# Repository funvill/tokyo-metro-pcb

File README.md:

# tokyo-metro-pcb

A printed circuit board that is a map of the Tokyo subway, with one
addressable RGB LED per station: Tokyo Metro's nine lines and Toei's four,
the two extensions under construction, the JR Yamanote loop, the Toden
Arakawa tram, the Yurikamome, the Rinkai line and the Shinkansen —
**248 stations, 248 LEDs**, on a 320 × 280 mm board.

The third board in the series, ported from the
[Montréal Métro PCB](https://github.com/funvill/montreal-skytrain-pcb), which
came from the
[Vancouver SkyTrain PCB](https://github.com/funvill/vancouver-skytrain-pcb).

The map is **organic**: every station stands where the city puts it (mean
error 6 m) and the track follows the real rails from OpenStreetMap, bridges
and tunnels included — the Rainbow Bridge with its Shibaura spiral, the
1,236 m Arakawa truss, the Tokyo Port Tunnel. Station names sit in capsules
that knock the route out behind them, so a name may lie across a line and
still read.

**Status: the map is finished, and the KiCad board is built from it —
placement, outline and artwork. Nothing is routed yet.**

*The KiCad board, rendered by `kicad-cli`. Not a preview: this is the
artwork as it would be plotted.*

## Where things are

| Folder | What |
|---|---|
| [`input/tokyo.json`](input/) | **The board.** Stations, lines, label placements, chain, water, wordmark |
| [`input/`](input/) | The builders, the Overpass queries, and the hand-made data |
| [`input/osm/`](input/osm/) | Raw Overpass responses, committed so builds run offline |
| [`fonts/`](fonts/) | Archivo Narrow SemiBold, the label face, SIL OFL |
| [`tools/`](tools/) | The pipeline: layout, labels, chain, checks, previews, fab outputs |
| [`hardware/`](hardware/) | KiCad 10 footprint and symbol libraries; the board is not built yet |
| [`firmware/`](firmware/) | XIAO firmware; the line table is generated from the data |
| [`docs/decisions.md`](docs/decisions.md) | Scope, board, labels, power, controller |
| [`docs/styles.md`](docs/styles.md) | The eight map styles considered, and everything settled since |
| [`runbook-new-city.md`](runbook-new-city.md) | The phase-by-phase process |
| [`lessons-learned.md`](lessons-learned.md) | Part D is this board; Part C is the pre-order checklist |

## Rebuilding the map

```bash
cd input && ./rebuild.sh
```

One command, from the cached Overpass responses to `tokyo.json` and the
previews. Every intermediate is disposable and none is kept.

Hand work is **not** regenerated: `label_overrides.json` (248 label
placements) and `chain.json` (the LED order) are re-applied on every build,
and the only way to change them is `import_labels.py` or `build_chain.py`,
deliberately (lesson B5).

| Step | Tool |
|---|---|
| Station list from OSM, cross-checked against the official station codes | `input/build_station_latlon.py` |
| Octolinear layout, land fitted rigidly, water, wordmark | `input/build_tokyo.py` |
| Move the board edge in without redrawing the map | `tools/crop_board.py` |
| Label placement | `tools/auto_label.py`, `tools/check_fit.py` |
| LED chain order | `tools/build_chain.py` |
| What the board will etch | `tools/preview_map.py` |
| Firmware line table | `tools/make_firmware_lines.py` |

## The board

| | |
|---|---|
| Size | 320 × 280 mm, 2 layers, ENIG |
| LEDs | 248 XL-1615 WS2812B, one per station |
| Lines | 18, drawn in 0.75 mm white silkscreen on their real alignment; the Shinkansen at 2.2× |
| Water | Bare ENIG copper, land placed rigidly at 14.4 mm/km, north up; no station's clearance disc notches it |
| Labels | English names, 1.1 mm, Archivo Narrow SemiBold **embedded in the board**, each in a knockout capsule; 242 of 248 plain horizontal, none rotated |
| Power | A USB-C input of its own, plus a 2-pin Phoenix Contact terminal block on a cuttable link |
| Controller | Seeed XIAO RP2040, hand-soldered at a board edge |

## Known, going into routing

- **67 LEDs sit in a hole cut out of the water**, so the front ground pour
  will be cut into islands and each of them needs its own via to the back
  plane. Script the island count; do not eyeball it (lesson A5, Part C.5).
- **38 chain hops cross bare-copper water**, 174 mm in total. None can run
  on the front.
- **25 label collisions remain** in the core, all but two white-on-white
  text over a route. They are hand work in KiCad, then frozen with
  `import_labels.py`.
- **248 LEDs is about 15 A at full white.** The firmware cap stays at
  900 mA until the supply and the injection points are proven.

## Still to do

1. Route by hand. Before starting: **67 LEDs sit in a hole cut out of the
   bare-copper water**, so the front pour is in islands and each needs its
   own via to the back plane; and **38 chain hops cross water**, which
   cannot be routed on the front.
2. Clear the DRC that is left: 2 shorts where mounting holes fall in the
   bay, 28 isolated copper islands, 16 starved thermals. The 11 "silkscreen
   clipped by board edge" warnings are the line stubs running off the edge
   on purpose, and the fab trims them.
3. The Part C checklist before ordering.

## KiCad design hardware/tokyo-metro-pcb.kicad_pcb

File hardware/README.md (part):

# Hardware (KiCad 10)

`tokyo-metro-pcb` — 320 × 280 mm, 2 layers, 248 WS2812B LEDs (XL-1615), one
per station, generated from [`../input/tokyo.json`](../input/tokyo.json).

Copied from the Montréal board and ported by the scripts in `../tools`.
**The schematic is built and verified, and the board is placed and has its
artwork. Nothing is routed.**

## State

| | |
|---|---|
| Schematic | 248 LEDs in 13 rows of 20, generated by `make_schematic.py`; 0 duplicate uuids; **0 overlapping symbols, labels or visible text** (`check_schematic.py`); regenerating is idempotent (byte-identical on a second run) |
| Chain | `U1 GPIO1 → LED_DATA → R1 → LED_IN → LED1 … LED248 → LED_OUT`, verified by `check_led_chain.py` — which now checks the **driver**, the **rails** and the **capacitors** too, not just the hops. Each of those was added after a bug it would have caught: the generator deleted `LED_DATA`/`LED_IN` off R1 and put nothing back (R1 floating, nothing driving the chain, PASS); a rail checked by *name* would pass with no source on it; and extending from 13 caps to 52 without extending the power rail left 39 of them floating, also PASS |
| Nets | 256 real nets; +5V 265 nodes, GND 272. 11 single-node nets, all deliberate: seven spare XIAO GPIOs, `3V3`, and the redundant pad of each 4-pad tactile switch |
| Controller | U1 (XIAO RP2040), R1 (330 Ω), C1 (100 µF 6.3 V, 1206), SW1–4, four test points, four M3 holes — all inherited from Montréal, wiring intact. U1's **Value says `XIAO-RP2040-DIP` but its footprint is the SMD/castellated land pattern** — a header module will not fit; reconcile before assembly |
| Decoupling | **52 caps, ROW0–ROW51** at `1uF,16V,X5R` in 0402, four per schematic row, each across the rails and spread along the chain by index so they land across the whole map. Was 13 — one per row of 20 LEDs, which is bulk rather than decoupling: the far LED sat nineteen pitches of trace from its cap and the east of the board was 74 mm from the nearest one. The old value, `10uF,10V,X5R` in an 0402, is not a buyable part; 1 µF 16 V in 0402 is |
| Board | 320 × 280 mm, r5 corners; Montréal's tracks and front art stripped; 1,118 art blocks written; schematic parity clean. One GND zone on F.Cu + B.Cu — there were three stacked copies with identical outlines, whose fills split arbitrarily by priority and accounted for all 32 `isolated_copper` reports |
| DRC | 0 shorts, 0 clearance, 0 isolated copper, 0 parity. Left: 16 `starved_thermal` (GND pads on cut-up islands, routing-stage), 11 `silk_edge_clearance` (art bleeding off the edge — intended, the fab clips it), 199 `solder_mask_bridge`. The mask-bridge check was set to `ignore` and is now `warning`: 199 of its 200 hits are pad-to-pad *inside* one LED footprint, whose own inter-pad gap is 0.250 mm, so this is a fab mask-dam question about the footprint, not an artwork bug |
| Placement | 248 LEDs at their stations, **all at one orientation (270°, pin 1 up)**; 52 decoupling capacitors; 4 M3 holes; controller group at (40, 220). They used to be turned individually so DOUT faced the next in the chain, which gave the router shorter hops but put the parts at eight different angles — and pads 1 and 4 share the part's long edge, so a 180° error swaps GND with DI and +5V with DO. One orientation makes the whole board a single thing to check |
| Routing | **nothing routed** — 547 unconnected pads. Note the DRC *report* says 499: its JSON omits 48 real ratsnest edges (the chain hops that cross the bay, and the four BUTTON nets), so **do not use "unconnected: 0" in the report as the routing-complete gate** — read `GetUnconnectedCount` from pcbnew instead |
| Firmware tables | `firmware_tables.h`: NUM_LEDS 248, 36 line/branch index arrays |

## Regenerating the schematic

```
cd ../tools
python -X utf8 make_schematic.py ../hardware/tokyo-metro-pcb.kicad_sch 248
```

`tokyo-metro-pcb.kicad_sch.template` is a **required input**: a pristine copy
of the Montréal sheet, committed alongside the schematic. The generator always
builds from it, never from its own last output - reading its own output moved
the generated power symbols outside the drop region and left 130 duplicate
uuids on the second run.

It rebuilds the whole LED section — symbols, rails, row decoupling caps,
chain wiring and the `CHAIN1`…`CHAIN12` row labels — and leaves the
controller block and the test-point column untouched. It is safe to re-run:
the second run drops what the first generated and produces the same bytes.

Three things it has to get right, each of which it got wrong first:

- **Keep the controller's wiring.** Dropping every wire on the sheet leaves
  U1, R1 and the test points floating, with nothing on `LED_IN` or
  `LED_OUT`. Only wires below `GRID_TOP` *and* right of `GRID_LEFT` belong
  to the grid; the test-point column runs down to y = 83 at x = 24.
- **Do not reuse Montréal's row label names.** Its last output was tied to
  the `LED_OUT` test point with a second label, `ROW8`. With 13 rows that
  collides, shorting LED160 to the chain output. Generated labels are
  `CHAIN*`, and stray `ROW*` labels are dropped.
- **Re-uuid every uuid in a cloned block**, not just the first. A symbol
  carries one per property, so cloning 248 LEDs left four uuids shared
  across all of them.

## Checking the schematic for overlaps

```
python -X utf8 ../tools/check_schematic.py tokyo-metro-pcb.kicad_sch -v
```

A generated sheet can be electrically perfect and unreadable: nothing in the
netlist notices a decoupling capacitor sitting on a global label, and KiCad's
ERC does not check it either. The checker takes each symbol's outline from
its `lib_symbols` definition, rotates and moves it to the instance, and adds
a box for every global label and every *visible* Reference and Value - the
hidden ones are metadata and counting them buries the real collisions in 900
false ones. It reports 710 placed items and 0 overlapping pairs.

Three overlaps it found, all now fixed in the generator:

- the row capacitors sat on their own row's input label (`x_cap = ox - 30.48`
  moves them clear), and then on the mounting-hole column (grid origin moved
  to `95,70`);
- Montréal's `LED_DATA` and `LED_IN` labels sat directly on R1's body,
  because they were placed on its pins with no wire at all - each now gets a
  5.08 mm stub wire;
- C1's Value text is 16 mm wide and the gap between U1 and the +5V symbol is
  14.5 mm, so it is moved to the clear band below the controller.

## Checking

```
"C:/Program Files/KiCad/10.0/bin/kicad-cli.exe" sch export netlist \
    --format kicadsexpr -o ../test-results/netlist.net tokyo-metro-pcb.kicad_sch
python -X utf8 ../tools/check_led_chain.py ../test-results/netlist.net 248
grep -o 'uuid "[^"]*"' tokyo-metro-pcb.kicad_sch | sort | uniq -d | wc -l   # 0
```

A netlist export that prints no warning means the annotation is clean; a
duplicate `#PWR` reference is what "schematic has annotation errors" means,
so the generated power symbols are numbered from `#PWR901` to stay clear of
the controller's own.

## Still to do

1. **The board.** `port_board.py --strip` on a fresh copy, then
   `reposition_board.py --board 320 --height 280`, then `export_art.py` and
   `mask_under_silk.py`.
2. The hand pass over the 25 remaining label collisions, then
   `import_labels.py` to freeze them.
3. **A way to get power in.** There is none: every `+5V` node is an LED, a
   cap, U1's VBUS, or a 3 × 3 mm test pad. The only real inputs are the
   XIAO's USB-C and two SMD test points, and neither passes amps. This is a
   schematic change plus a board re-import — cheap now, painful after
   routing. Decide the LED current first: 248 × 60 mA (the 5050 WS2812B
   figure) is 15 A, but the XL-1615 is a 1.6 × 1.5 mm part and is likely
   well under 20 mA full-white, which would put the board nearer 4–5 A. No
   datasheet is in the repo and the symbol's Datasheet field is empty.
4. Routing, by hand. Note before starting: **44 LEDs sit in holes cut out of
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
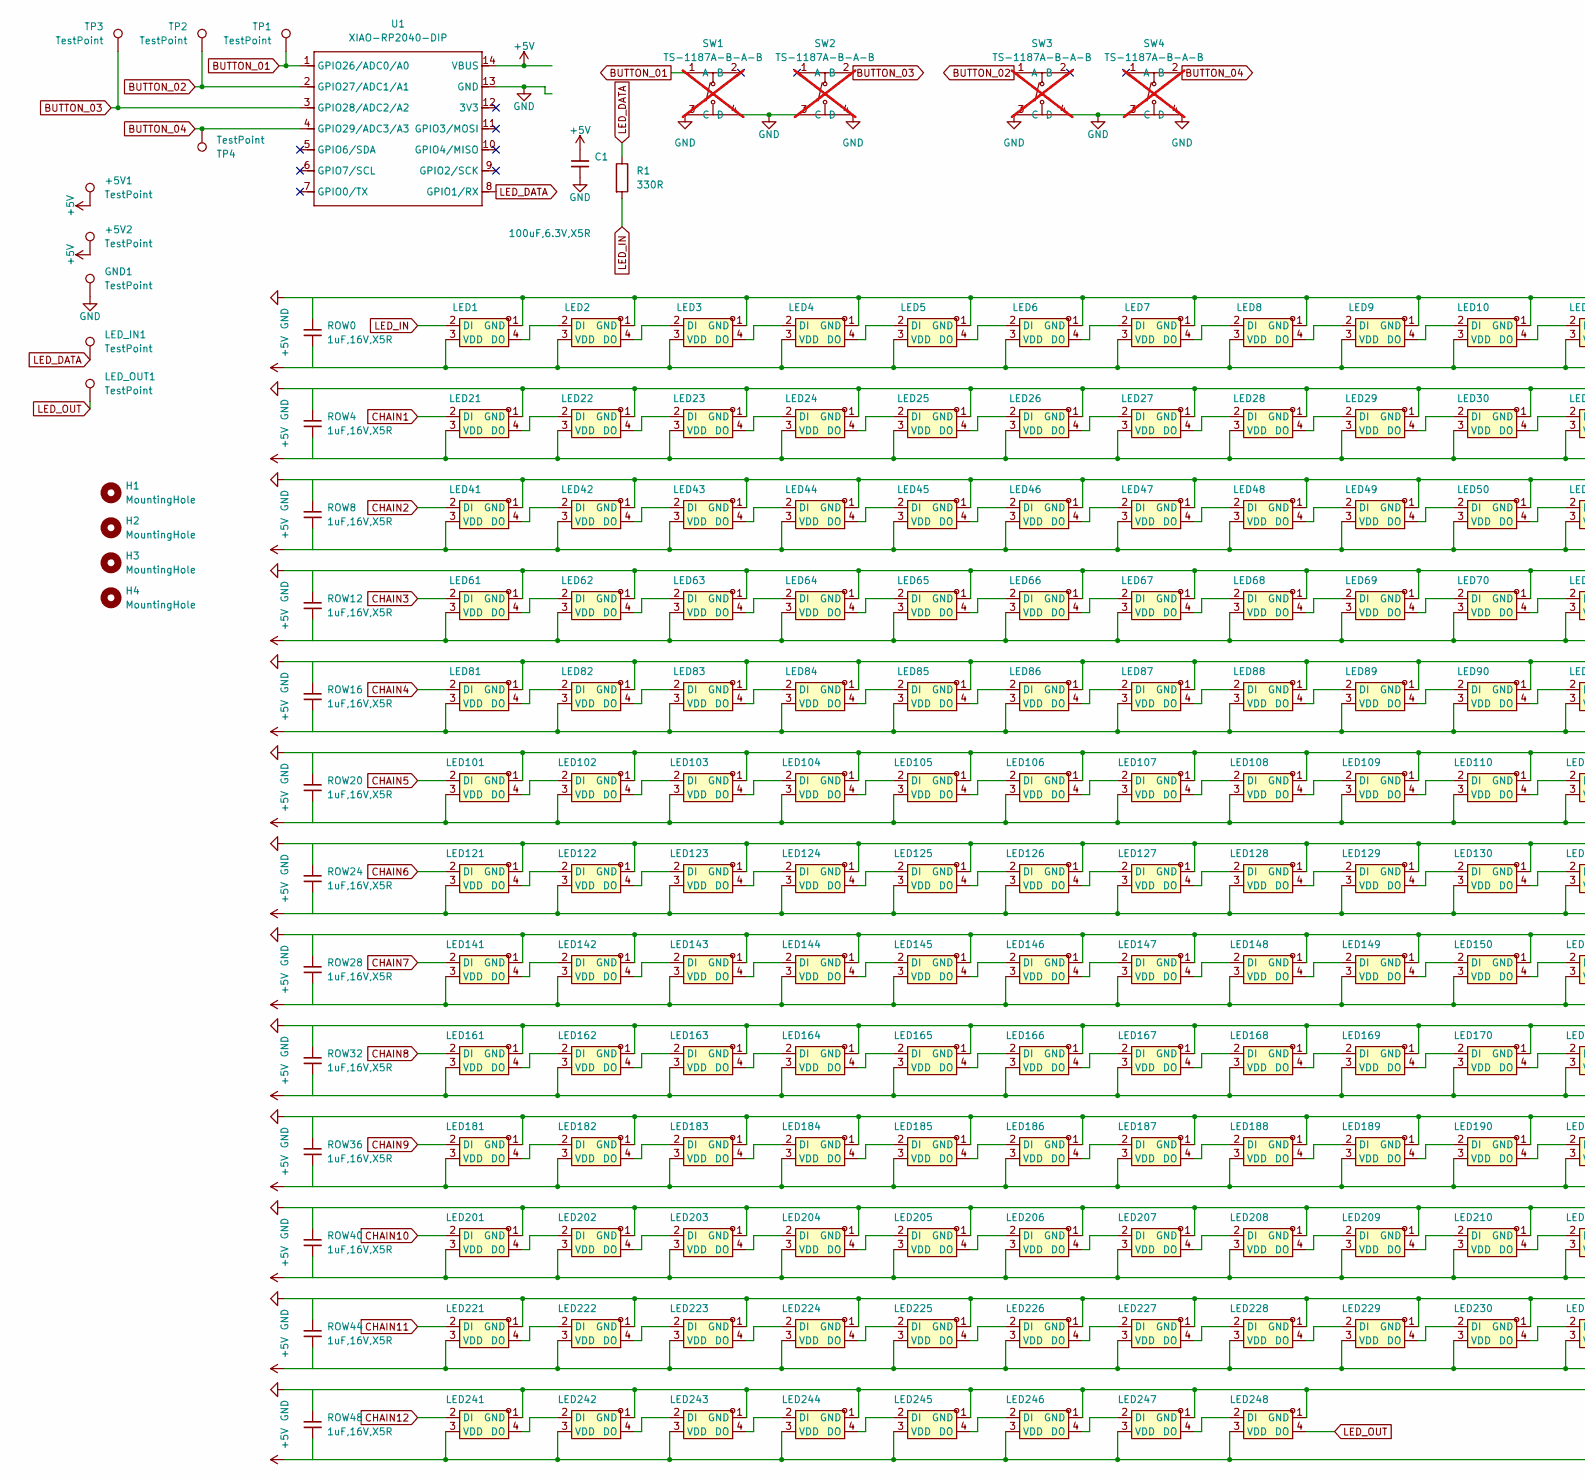
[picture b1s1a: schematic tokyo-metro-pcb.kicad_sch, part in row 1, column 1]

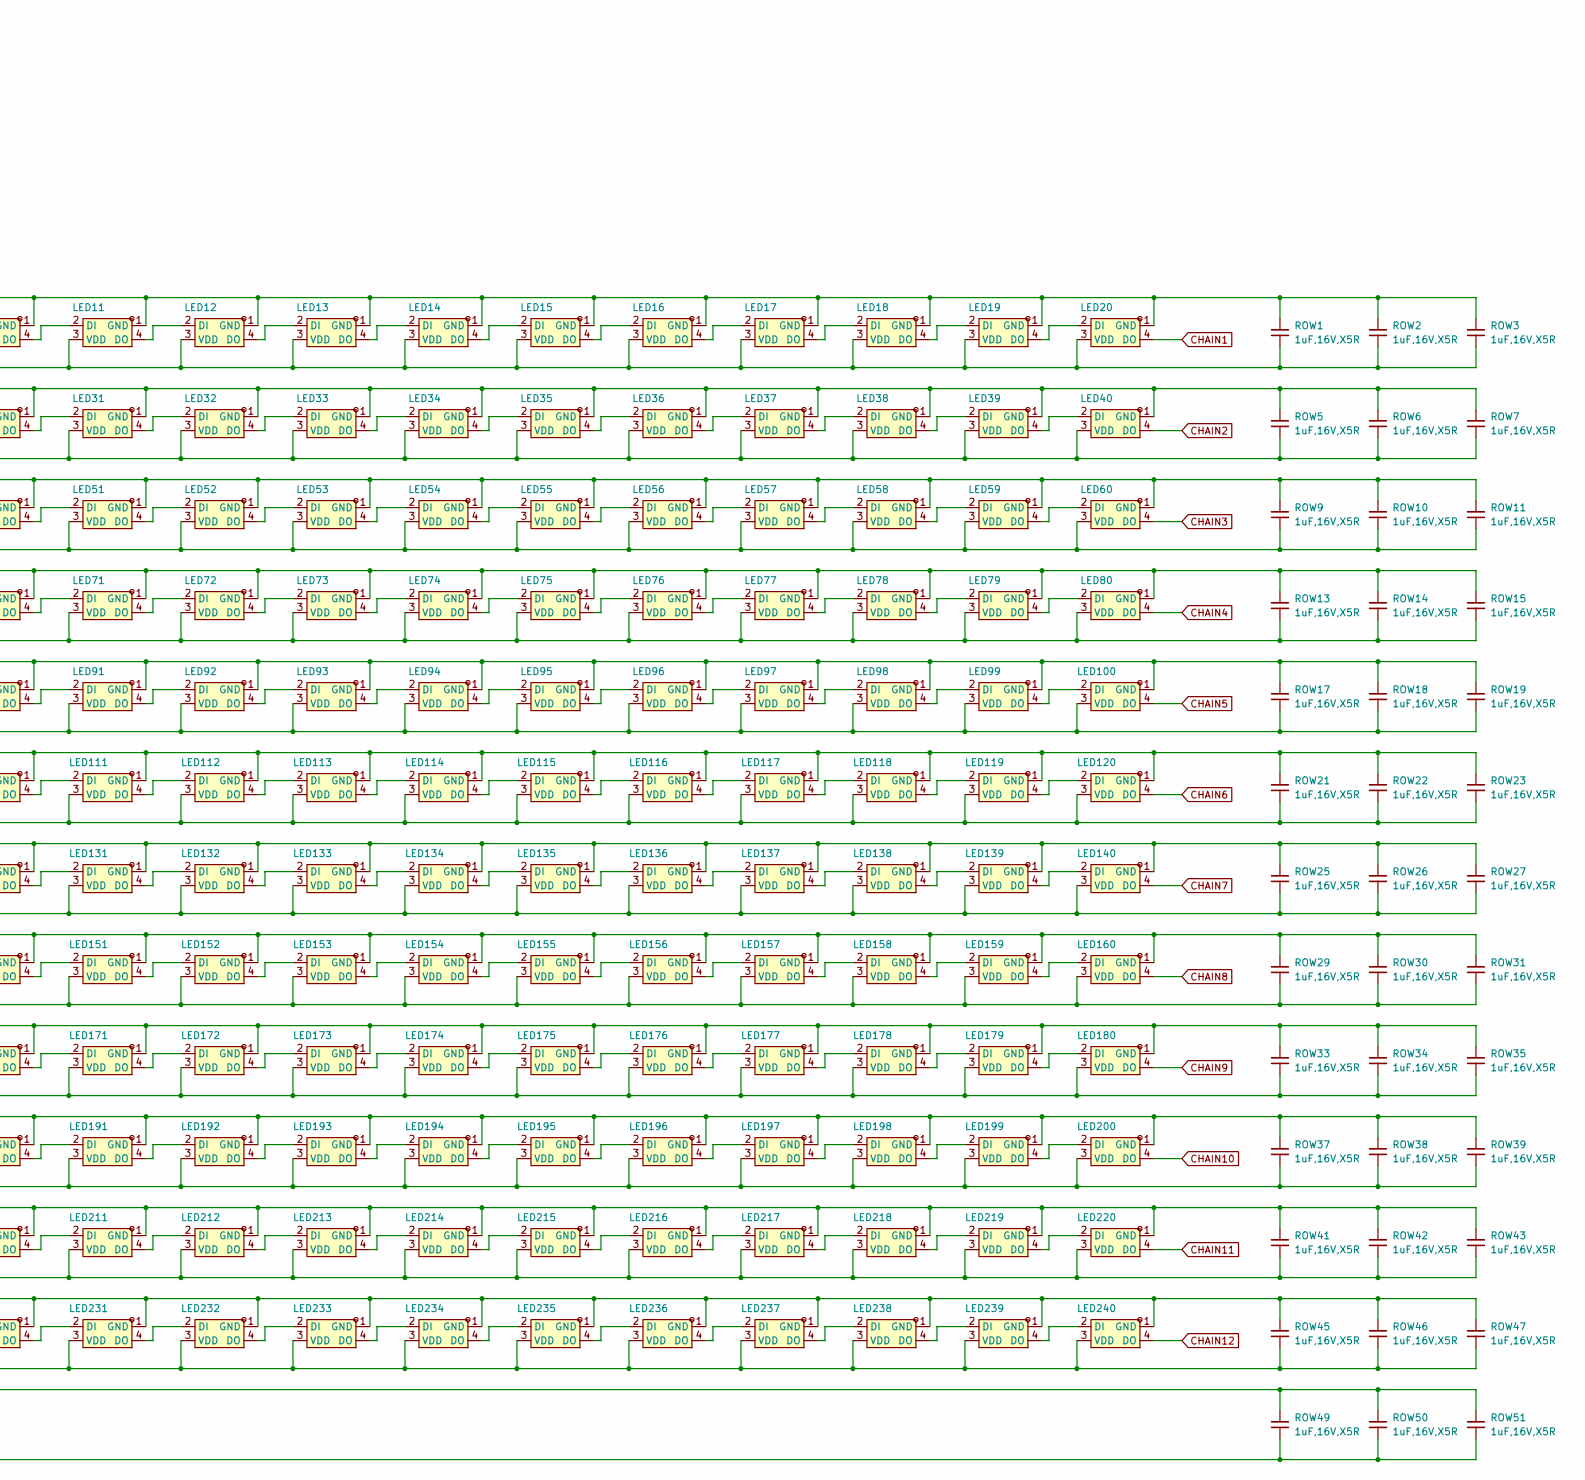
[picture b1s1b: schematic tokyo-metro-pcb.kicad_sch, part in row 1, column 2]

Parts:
+5V1, +5V2: TestPoint; TestPoint_Pad_3.0x3.0mm
C1: 100uF,6.3V,X5R; C_1206_3216Metric; MFGPN CL31A107MQHNNNE; LCSC C15008
GND1: TestPoint; TestPoint_Pad_3.0x3.0mm
H1, H2, H3, H4: MountingHole; MountingHole_3.2mm_M3_DIN965_Pad_TopBottom
LED1, LED2, LED3, LED4, LED5, LED6, LED7, LED8, LED9, LED10, LED11, LED12, LED13, LED14, LED15, LED16, LED17, LED18, LED19, LED20, LED21, LED22, LED23, LED24, LED25, LED26, LED27, LED28, LED29, LED30, LED31, LED32, LED33, LED34, LED35, LED36, LED37, LED38, LED39, LED40, LED41, LED42, LED43, LED44, LED45, LED46, LED47, LED48, LED49, LED50, LED51, LED52, LED53, LED54, LED55, LED56, LED57, LED58, LED59, LED60, LED61, LED62, LED63, LED64, LED65, LED66, LED67, LED68, LED69, LED70, LED71, LED72, LED73, LED74, LED75, LED76, LED77, LED78, LED79, LED80, LED81, LED82, LED83, LED84, LED85, LED86, LED87, LED88, LED89, LED90, LED91, LED92, LED93, LED94, LED95, LED96, LED97, LED98, LED99, LED100, LED101, LED102, LED103, LED104, LED105, LED106, LED107, LED108, LED109, LED110, LED111, LED112, LED113, LED114, LED115, LED116, LED117, LED118, LED119, LED120, LED121, LED122, LED123, LED124, LED125, LED126, LED127, LED128, LED129, LED130, LED131, LED132, LED133, LED134, LED135, LED136, LED137, LED138, LED139, LED140, LED141, LED142, LED143, LED144, LED145, LED146, LED147, LED148, LED149, LED150, LED151, LED152, LED153, LED154, LED155, LED156, LED157, LED158, LED159, LED160, LED161, LED162, LED163, LED164, LED165, LED166, LED167, LED168, LED169, LED170, LED171, LED172, LED173, LED174, LED175, LED176, LED177, LED178, LED179, LED180, LED181, LED182, LED183, LED184, LED185, LED186, LED187, LED188, LED189, LED190, LED191, LED192, LED193, LED194, LED195, LED196, LED197, LED198, LED199, LED200, LED201, LED202, LED203, LED204, LED205, LED206, LED207, LED208, LED209, LED210, LED211, LED212, LED213, LED214, LED215, LED216, LED217, LED218, LED219, LED220, LED221, LED222, LED223, LED224, LED225, LED226, LED227, LED228, LED229, LED230, LED231, LED232, LED233, LED234, LED235, LED236, LED237, LED238, LED239, LED240, LED241, LED242, LED243, LED244, LED245, LED246, LED247, LED248: XL-1615RGBC-WS2812B; LED-SMD_4P-L1.6-W1.5_XL-1615RGBC-WS2812B-1; LCSC Part C5349954
LED_IN1: TestPoint; TestPoint_Pad_3.0x3.0mm
LED_OUT1: TestPoint; TestPoint_Pad_3.0x3.0mm
R1: 330R; R_0402_1005Metric; MFGPN 0402WGF3300TCE; LCSC C25104
ROW0, ROW1, ROW2, ROW3, ROW4, ROW5, ROW6, ROW7, ROW8, ROW9, ROW10, ROW11, ROW12, ROW13, ROW14, ROW15, ROW16, ROW17, ROW18, ROW19, ROW20, ROW21, ROW22, ROW23, ROW24, ROW25, ROW26, ROW27, ROW28, ROW29, ROW30, ROW31, ROW32, ROW33, ROW34, ROW35, ROW36, ROW37, ROW38, ROW39, ROW40, ROW41, ROW42, ROW43, ROW44, ROW45, ROW46, ROW47, ROW48, ROW49, ROW50, ROW51: 1uF,16V,X5R; C_0402_1005Metric; MFGPN CL05A105KA5NQNC; LCSC C52923
SW1, SW2, SW3, SW4: TS-1187A-B-A-B; SW-SMD_4P-L5.1-W5.1-P3.70-LS6.5-TL_H1.5; LCSC Part C318884; not fitted
TP1, TP2, TP3, TP4: TestPoint; TestPoint_Pad_3.0x3.0mm
U1: XIAO-RP2040-DIP; XIAO-RP2040-SMD

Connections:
+5V: +5V1.1 (1_1), +5V2.1 (1_1), C1.1, LED1.3 (VDD), LED2.3 (VDD), LED3.3 (VDD), LED4.3 (VDD), LED5.3 (VDD), LED6.3 (VDD), LED7.3 (VDD), LED8.3 (VDD), LED9.3 (VDD), LED10.3 (VDD), LED11.3 (VDD), LED12.3 (VDD), LED13.3 (VDD), LED14.3 (VDD), LED15.3 (VDD), LED16.3 (VDD), LED17.3 (VDD), LED18.3 (VDD), LED19.3 (VDD), LED20.3 (VDD), LED21.3 (VDD), LED22.3 (VDD), LED23.3 (VDD), LED24.3 (VDD), LED25.3 (VDD), LED26.3 (VDD), LED27.3 (VDD), LED28.3 (VDD), LED29.3 (VDD), LED30.3 (VDD), LED31.3 (VDD), LED32.3 (VDD), LED33.3 (VDD), LED34.3 (VDD), LED35.3 (VDD), LED36.3 (VDD), LED37.3 (VDD), LED38.3 (VDD), LED39.3 (VDD), LED40.3 (VDD), LED41.3 (VDD), LED42.3 (VDD), LED43.3 (VDD), LED44.3 (VDD), LED45.3 (VDD), LED46.3 (VDD), LED47.3 (VDD), LED48.3 (VDD), LED49.3 (VDD), LED50.3 (VDD), LED51.3 (VDD), LED52.3 (VDD), LED53.3 (VDD), LED54.3 (VDD), LED55.3 (VDD), LED56.3 (VDD), LED57.3 (VDD), LED58.3 (VDD), LED59.3 (VDD), LED60.3 (VDD), LED61.3 (VDD), LED62.3 (VDD), LED63.3 (VDD), LED64.3 (VDD), LED65.3 (VDD), LED66.3 (VDD), LED67.3 (VDD), LED68.3 (VDD), LED69.3 (VDD), LED70.3 (VDD), LED71.3 (VDD), LED72.3 (VDD), LED73.3 (VDD), LED74.3 (VDD), LED75.3 (VDD), LED76.3 (VDD), LED77.3 (VDD), LED78.3 (VDD), LED79.3 (VDD), LED80.3 (VDD), LED81.3 (VDD), LED82.3 (VDD), LED83.3 (VDD), LED84.3 (VDD), LED85.3 (VDD), LED86.3 (VDD), LED87.3 (VDD), LED88.3 (VDD), LED89.3 (VDD), LED90.3 (VDD), LED91.3 (VDD), LED92.3 (VDD), LED93.3 (VDD), LED94.3 (VDD), LED95.3 (VDD), LED96.3 (VDD), LED97.3 (VDD), LED98.3 (VDD), LED99.3 (VDD), LED100.3 (VDD), LED101.3 (VDD), LED102.3 (VDD), LED103.3 (VDD), LED104.3 (VDD), LED105.3 (VDD), LED106.3 (VDD), LED107.3 (VDD), LED108.3 (VDD), LED109.3 (VDD), LED110.3 (VDD), LED111.3 (VDD), LED112.3 (VDD), LED113.3 (VDD), LED114.3 (VDD), LED115.3 (VDD), LED116.3 (VDD), LED117.3 (VDD), LED118.3 (VDD), LED119.3 (VDD), LED120.3 (VDD), LED121.3 (VDD), LED122.3 (VDD), LED123.3 (VDD), LED124.3 (VDD), LED125.3 (VDD), LED126.3 (VDD), LED127.3 (VDD), LED128.3 (VDD), LED129.3 (VDD), LED130.3 (VDD), LED131.3 (VDD), LED132.3 (VDD), LED133.3 (VDD), LED134.3 (VDD), LED135.3 (VDD), LED136.3 (VDD), LED137.3 (VDD), LED138.3 (VDD), LED139.3 (VDD), LED140.3 (VDD), LED141.3 (VDD), LED142.3 (VDD), LED143.3 (VDD), LED144.3 (VDD), LED145.3 (VDD), LED146.3 (VDD), LED147.3 (VDD), LED148.3 (VDD), LED149.3 (VDD), LED150.3 (VDD), LED151.3 (VDD), LED152.3 (VDD), LED153.3 (VDD), LED154.3 (VDD), LED155.3 (VDD), LED156.3 (VDD), LED157.3 (VDD), LED158.3 (VDD), LED159.3 (VDD), LED160.3 (VDD), LED161.3 (VDD), LED162.3 (VDD), LED163.3 (VDD), LED164.3 (VDD), LED165.3 (VDD), LED166.3 (VDD), LED167.3 (VDD), LED168.3 (VDD), LED169.3 (VDD), LED170.3 (VDD), LED171.3 (VDD), LED172.3 (VDD), LED173.3 (VDD), LED174.3 (VDD), LED175.3 (VDD), LED176.3 (VDD), LED177.3 (VDD), LED178.3 (VDD), LED179.3 (VDD), LED180.3 (VDD), LED181.3 (VDD), LED182.3 (VDD), LED183.3 (VDD), LED184.3 (VDD), LED185.3 (VDD), LED186.3 (VDD), LED187.3 (VDD), LED188.3 (VDD), LED189.3 (VDD), LED190.3 (VDD), LED191.3 (VDD), LED192.3 (VDD), LED193.3 (VDD), LED194.3 (VDD), LED195.3 (VDD), LED196.3 (VDD), LED197.3 (VDD), LED198.3 (VDD), LED199.3 (VDD), LED200.3 (VDD), LED201.3 (VDD), LED202.3 (VDD), LED203.3 (VDD), LED204.3 (VDD), LED205.3 (VDD), LED206.3 (VDD), LED207.3 (VDD), LED208.3 (VDD), LED209.3 (VDD), LED210.3 (VDD), LED211.3 (VDD), LED212.3 (VDD), LED213.3 (VDD), LED214.3 (VDD), LED215.3 (VDD), LED216.3 (VDD), LED217.3 (VDD), LED218.3 (VDD), LED219.3 (VDD), LED220.3 (VDD), LED221.3 (VDD), LED222.3 (VDD), LED223.3 (VDD), LED224.3 (VDD), LED225.3 (VDD), LED226.3 (VDD), LED227.3 (VDD), LED228.3 (VDD), LED229.3 (VDD), LED230.3 (VDD), LED231.3 (VDD), LED232.3 (VDD), LED233.3 (VDD), LED234.3 (VDD), LED235.3 (VDD), LED236.3 (VDD), LED237.3 (VDD), LED238.3 (VDD), LED239.3 (VDD), LED240.3 (VDD), LED241.3 (VDD), LED242.3 (VDD), LED243.3 (VDD), LED244.3 (VDD), LED245.3 (VDD), LED246.3 (VDD), LED247.3 (VDD), LED248.3 (VDD), ROW0.2, ROW1.2, ROW2.2, ROW3.2, ROW4.2, ROW5.2, ROW6.2, ROW7.2, ROW8.2, ROW9.2, ROW10.2, ROW11.2, ROW12.2, ROW13.2, ROW14.2, ROW15.2, ROW16.2, ROW17.2, ROW18.2, ROW19.2, ROW20.2, ROW21.2, ROW22.2, ROW23.2, ROW24.2, ROW25.2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
BUTTON_01: SW1.1 (A), TP1.1 (1_1), U1.1 (GPIO26/ADC0/A0)
BUTTON_02: SW3.1 (A), TP2.1 (1_1), U1.2 (GPIO27/ADC1/A1)
BUTTON_03: SW2.2 (B), TP3.1 (1_1), U1.3 (GPIO28/ADC2/A2)
BUTTON_04: SW4.2 (B), TP4.1 (1_1), U1.4 (GPIO29/ADC3/A3)
CHAIN1: LED20.4 (DO), LED21.2 (DI)
CHAIN2: LED40.4 (DO), LED41.2 (DI)
CHAIN3: LED60.4 (DO), LED61.2 (DI)
CHAIN4: LED80.4 (DO), LED81.2 (DI)
CHAIN5: LED100.4 (DO), LED101.2 (DI)
CHAIN6: LED120.4 (DO), LED121.2 (DI)
CHAIN7: LED140.4 (DO), LED141.2 (DI)
CHAIN8: LED160.4 (DO), LED161.2 (DI)
CHAIN9: LED180.4 (DO), LED181.2 (DI)
CHAIN10: LED200.4 (DO), LED201.2 (DI)
CHAIN11: LED220.4 (DO), LED221.2 (DI)
CHAIN12: LED240.4 (DO), LED241.2 (DI)
GND: C1.2, GND1.1 (1_1), LED1.1 (GND), LED2.1 (GND), LED3.1 (GND), LED4.1 (GND), LED5.1 (GND), LED6.1 (GND), LED7.1 (GND), LED8.1 (GND), LED9.1 (GND), LED10.1 (GND), LED11.1 (GND), LED12.1 (GND), LED13.1 (GND), LED14.1 (GND), LED15.1 (GND), LED16.1 (GND), LED17.1 (GND), LED18.1 (GND), LED19.1 (GND), LED20.1 (GND), LED21.1 (GND), LED22.1 (GND), LED23.1 (GND), LED24.1 (GND), LED25.1 (GND), LED26.1 (GND), LED27.1 (GND), LED28.1 (GND), LED29.1 (GND), LED30.1 (GND), LED31.1 (GND), LED32.1 (GND), LED33.1 (GND), LED34.1 (GND), LED35.1 (GND), LED36.1 (GND), LED37.1 (GND), LED38.1 (GND), LED39.1 (GND), LED40.1 (GND), LED41.1 (GND), LED42.1 (GND), LED43.1 (GND), LED44.1 (GND), LED45.1 (GND), LED46.1 (GND), LED47.1 (GND), LED48.1 (GND), LED49.1 (GND), LED50.1 (GND), LED51.1 (GND), LED52.1 (GND), LED53.1 (GND), LED54.1 (GND), LED55.1 (GND), LED56.1 (GND), LED57.1 (GND), LED58.1 (GND), LED59.1 (GND), LED60.1 (GND), LED61.1 (GND), LED62.1 (GND), LED63.1 (GND), LED64.1 (GND), LED65.1 (GND), LED66.1 (GND), LED67.1 (GND), LED68.1 (GND), LED69.1 (GND), LED70.1 (GND), LED71.1 (GND), LED72.1 (GND), LED73.1 (GND), LED74.1 (GND), LED75.1 (GND), LED76.1 (GND), LED77.1 (GND), LED78.1 (GND), LED79.1 (GND), LED80.1 (GND), LED81.1 (GND), LED82.1 (GND), LED83.1 (GND), LED84.1 (GND), LED85.1 (GND), LED86.1 (GND), LED87.1 (GND), LED88.1 (GND), LED89.1 (GND), LED90.1 (GND), LED91.1 (GND), LED92.1 (GND), LED93.1 (GND), LED94.1 (GND), LED95.1 (GND), LED96.1 (GND), LED97.1 (GND), LED98.1 (GND), LED99.1 (GND), LED100.1 (GND), LED101.1 (GND), LED102.1 (GND), LED103.1 (GND), LED104.1 (GND), LED105.1 (GND), LED106.1 (GND), LED107.1 (GND), LED108.1 (GND), LED109.1 (GND), LED110.1 (GND), LED111.1 (GND), LED112.1 (GND), LED113.1 (GND), LED114.1 (GND), LED115.1 (GND), LED116.1 (GND), LED117.1 (GND), LED118.1 (GND), LED119.1 (GND), LED120.1 (GND), LED121.1 (GND), LED122.1 (GND), LED123.1 (GND), LED124.1 (GND), LED125.1 (GND), LED126.1 (GND), LED127.1 (GND), LED128.1 (GND), LED129.1 (GND), LED130.1 (GND), LED131.1 (GND), LED132.1 (GND), LED133.1 (GND), LED134.1 (GND), LED135.1 (GND), LED136.1 (GND), LED137.1 (GND), LED138.1 (GND), LED139.1 (GND), LED140.1 (GND), LED141.1 (GND), LED142.1 (GND), LED143.1 (GND), LED144.1 (GND), LED145.1 (GND), LED146.1 (GND), LED147.1 (GND), LED148.1 (GND), LED149.1 (GND), LED150.1 (GND), LED151.1 (GND), LED152.1 (GND), LED153.1 (GND), LED154.1 (GND), LED155.1 (GND), LED156.1 (GND), LED157.1 (GND), LED158.1 (GND), LED159.1 (GND), LED160.1 (GND), LED161.1 (GND), LED162.1 (GND), LED163.1 (GND), LED164.1 (GND), LED165.1 (GND), LED166.1 (GND), LED167.1 (GND), LED168.1 (GND), LED169.1 (GND), LED170.1 (GND), LED171.1 (GND), LED172.1 (GND), LED173.1 (GND), LED174.1 (GND), LED175.1 (GND), LED176.1 (GND), LED177.1 (GND), LED178.1 (GND), LED179.1 (GND), LED180.1 (GND), LED181.1 (GND), LED182.1 (GND), LED183.1 (GND), LED184.1 (GND), LED185.1 (GND), LED186.1 (GND), LED187.1 (GND), LED188.1 (GND), LED189.1 (GND), LED190.1 (GND), LED191.1 (GND), LED192.1 (GND), LED193.1 (GND), LED194.1 (GND), LED195.1 (GND), LED196.1 (GND), LED197.1 (GND), LED198.1 (GND), LED199.1 (GND), LED200.1 (GND), LED201.1 (GND), LED202.1 (GND), LED203.1 (GND), LED204.1 (GND), LED205.1 (GND), LED206.1 (GND), LED207.1 (GND), LED208.1 (GND), LED209.1 (GND), LED210.1 (GND), LED211.1 (GND), LED212.1 (GND), LED213.1 (GND), LED214.1 (GND), LED215.1 (GND), LED216.1 (GND), LED217.1 (GND), LED218.1 (GND), LED219.1 (GND), LED220.1 (GND), LED221.1 (GND), LED222.1 (GND), LED223.1 (GND), LED224.1 (GND), LED225.1 (GND), LED226.1 (GND), LED227.1 (GND), LED228.1 (GND), LED229.1 (GND), LED230.1 (GND), LED231.1 (GND), LED232.1 (GND), LED233.1 (GND), LED234.1 (GND), LED235.1 (GND), LED236.1 (GND), LED237.1 (GND), LED238.1 (GND), LED239.1 (GND), LED240.1 (GND), LED241.1 (GND), LED242.1 (GND), LED243.1 (GND), LED244.1 (GND), LED245.1 (GND), LED246.1 (GND), LED247.1 (GND), LED248.1 (GND), ROW0.1, ROW1.1, ROW2.1, ROW3.1, ROW4.1, ROW5.1, ROW6.1, ROW7.1, ROW8.1, ROW9.1, ROW10.1, ROW11.1, ROW12.1, ROW13.1, ROW14.1, ROW15.1, ROW16.1, ROW17.1, ROW18.1, ROW19.1, ROW20.1, ROW21.1, ROW22.1, ROW23.1, ROW24.1, ROW25.1, ROW26.1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
LED_DATA: LED_IN1.1 (1_1), R1.1, U1.8 (GPIO1/RX)
LED_IN: LED1.2 (DI), R1.2
LED_OUT: LED248.4 (DO), LED_OUT1.1 (1_1)
unnamed: LED1.4 (DO), LED2.2 (DI)
unnamed: LED2.4 (DO), LED3.2 (DI)
unnamed: LED3.4 (DO), LED4.2 (DI)
unnamed: LED4.4 (DO), LED5.2 (DI)
unnamed: LED5.4 (DO), LED6.2 (DI)
unnamed: LED6.4 (DO), LED7.2 (DI)
unnamed: LED7.4 (DO), LED8.2 (DI)
unnamed: LED8.4 (DO), LED9.2 (DI)
unnamed: LED9.4 (DO), LED10.2 (DI)
unnamed: LED10.4 (DO), LED11.2 (DI)
unnamed: LED11.4 (DO), LED12.2 (DI)
unnamed: LED12.4 (DO), LED13.2 (DI)
unnamed: LED13.4 (DO), LED14.2 (DI)
unnamed: LED14.4 (DO), LED15.2 (DI)
unnamed: LED15.4 (DO), LED16.2 (DI)
unnamed: LED16.4 (DO), LED17.2 (DI)
unnamed: LED17.4 (DO), LED18.2 (DI)
unnamed: LED18.4 (DO), LED19.2 (DI)
unnamed: LED19.4 (DO), LED20.2 (DI)
unnamed: LED21.4 (DO), LED22.2 (DI)
unnamed: LED22.4 (DO), LED23.2 (DI)
unnamed: LED23.4 (DO), LED24.2 (DI)
unnamed: LED24.4 (DO), LED25.2 (DI)
unnamed: LED25.4 (DO), LED26.2 (DI)
unnamed: LED26.4 (DO), LED27.2 (DI)
unnamed: LED27.4 (DO), LED28.2 (DI)
unnamed: LED28.4 (DO), LED29.2 (DI)
unnamed: LED29.4 (DO), LED30.2 (DI)
unnamed: LED30.4 (DO), LED31.2 (DI)
unnamed: LED31.4 (DO), LED32.2 (DI)
unnamed: LED32.4 (DO), LED33.2 (DI)
unnamed: LED33.4 (DO), LED34.2 (DI)
unnamed: LED34.4 (DO), LED35.2 (DI)
unnamed: LED35.4 (DO), LED36.2 (DI)
unnamed: LED36.4 (DO), LED37.2 (DI)
unnamed: LED37.4 (DO), LED38.2 (DI)
unnamed: LED38.4 (DO), LED39.2 (DI)
unnamed: LED39.4 (DO), LED40.2 (DI)
unnamed: LED41.4 (DO), LED42.2 (DI)
unnamed: LED42.4 (DO), LED43.2 (DI)
unnamed: LED43.4 (DO), LED44.2 (DI)
unnamed: LED44.4 (DO), LED45.2 (DI)
unnamed: LED45.4 (DO), LED46.2 (DI)
unnamed: LED46.4 (DO), LED47.2 (DI)
unnamed: LED47.4 (DO), LED48.2 (DI)
unnamed: LED48.4 (DO), LED49.2 (DI)
unnamed: LED49.4 (DO), LED50.2 (DI)
unnamed: LED50.4 (DO), LED51.2 (DI)
unnamed: LED51.4 (DO), LED52.2 (DI)
unnamed: LED52.4 (DO), LED53.2 (DI)
unnamed: LED53.4 (DO), LED54.2 (DI)
unnamed: LED54.4 (DO), LED55.2 (DI)
unnamed: LED55.4 (DO), LED56.2 (DI)
unnamed: LED56.4 (DO), LED57.2 (DI)
unnamed: LED57.4 (DO), LED58.2 (DI)
unnamed: LED58.4 (DO), LED59.2 (DI)
unnamed: LED59.4 (DO), LED60.2 (DI)
unnamed: LED61.4 (DO), LED62.2 (DI)
unnamed: LED62.4 (DO), LED63.2 (DI)
unnamed: LED63.4 (DO), LED64.2 (DI)
unnamed: LED64.4 (DO), LED65.2 (DI)
unnamed: LED65.4 (DO), LED66.2 (DI)
unnamed: LED66.4 (DO), LED67.2 (DI)
unnamed: LED67.4 (DO), LED68.2 (DI)
unnamed: LED68.4 (DO), LED69.2 (DI)
unnamed: LED69.4 (DO), LED70.2 (DI)
unnamed: LED70.4 (DO), LED71.2 (DI)
unnamed: LED71.4 (DO), LED72.2 (DI)
unnamed: LED72.4 (DO), LED73.2 (DI)
unnamed: LED73.4 (DO), LED74.2 (DI)
unnamed: LED74.4 (DO), LED75.2 (DI)
unnamed: LED75.4 (DO), LED76.2 (DI)
unnamed: LED76.4 (DO), LED77.2 (DI)
unnamed: LED77.4 (DO), LED78.2 (DI)
unnamed: LED78.4 (DO), LED79.2 (DI)
unnamed: LED79.4 (DO), LED80.2 (DI)
unnamed: LED81.4 (DO), LED82.2 (DI)
unnamed: LED82.4 (DO), LED83.2 (DI)
unnamed: LED83.4 (DO), LED84.2 (DI)
unnamed: LED84.4 (DO), LED85.2 (DI)
unnamed: LED85.4 (DO), LED86.2 (DI)
unnamed: LED86.4 (DO), LED87.2 (DI)
unnamed: LED87.4 (DO), LED88.2 (DI)
unnamed: LED88.4 (DO), LED89.2 (DI)
unnamed: LED89.4 (DO), LED90.2 (DI)
unnamed: LED90.4 (DO), LED91.2 (DI)
unnamed: LED91.4 (DO), LED92.2 (DI)
unnamed: LED92.4 (DO), LED93.2 (DI)
unnamed: LED93.4 (DO), LED94.2 (DI)
unnamed: LED94.4 (DO), LED95.2 (DI)
unnamed: LED95.4 (DO), LED96.2 (DI)
unnamed: LED96.4 (DO), LED97.2 (DI)
unnamed: LED97.4 (DO), LED98.2 (DI)
unnamed: LED98.4 (DO), LED99.2 (DI)
unnamed: LED99.4 (DO), LED100.2 (DI)
unnamed: LED101.4 (DO), LED102.2 (DI)
unnamed: LED102.4 (DO), LED103.2 (DI)
unnamed: LED103.4 (DO), LED104.2 (DI)
unnamed: LED104.4 (DO), LED105.2 (DI)
unnamed: LED105.4 (DO), LED106.2 (DI)
unnamed: LED106.4 (DO), LED107.2 (DI)
unnamed: LED107.4 (DO), LED108.2 (DI)
unnamed: LED108.4 (DO), LED109.2 (DI)
unnamed: LED109.4 (DO), LED110.2 (DI)
unnamed: LED110.4 (DO), LED111.2 (DI)
unnamed: LED111.4 (DO), LED112.2 (DI)
unnamed: LED112.4 (DO), LED113.2 (DI)
unnamed: LED113.4 (DO), LED114.2 (DI)
unnamed: LED114.4 (DO), LED115.2 (DI)
unnamed: LED115.4 (DO), LED116.2 (DI)
unnamed: LED116.4 (DO), LED117.2 (DI)
unnamed: LED117.4 (DO), LED118.2 (DI)
unnamed: LED118.4 (DO), LED119.2 (DI)
unnamed: LED119.4 (DO), LED120.2 (DI)
unnamed: LED121.4 (DO), LED122.2 (DI)
unnamed: LED122.4 (DO), LED123.2 (DI)
unnamed: LED123.4 (DO), LED124.2 (DI)
unnamed: LED124.4 (DO), LED125.2 (DI)
unnamed: LED125.4 (DO), LED126.2 (DI)
unnamed: LED126.4 (DO), LED127.2 (DI)
unnamed: LED127.4 (DO), LED128.2 (DI)
unnamed: LED128.4 (DO), LED129.2 (DI)
unnamed: LED129.4 (DO), LED130.2 (DI)
unnamed: LED130.4 (DO), LED131.2 (DI)
unnamed: LED131.4 (DO), LED132.2 (DI)
unnamed: LED132.4 (DO), LED133.2 (DI)
unnamed: LED133.4 (DO), LED134.2 (DI)
unnamed: LED134.4 (DO), LED135.2 (DI)
unnamed: LED135.4 (DO), LED136.2 (DI)
unnamed: LED136.4 (DO), LED137.2 (DI)
unnamed: LED137.4 (DO), LED138.2 (DI)
unnamed: LED138.4 (DO), LED139.2 (DI)
unnamed: LED139.4 (DO), LED140.2 (DI)
unnamed: LED141.4 (DO), LED142.2 (DI)
unnamed: LED142.4 (DO), LED143.2 (DI)
unnamed: LED143.4 (DO), LED144.2 (DI)
unnamed: LED144.4 (DO), LED145.2 (DI)
unnamed: LED145.4 (DO), LED146.2 (DI)
unnamed: LED146.4 (DO), LED147.2 (DI)
unnamed: LED147.4 (DO), LED148.2 (DI)
unnamed: LED148.4 (DO), LED149.2 (DI)
unnamed: LED149.4 (DO), LED150.2 (DI)
unnamed: LED150.4 (DO), LED151.2 (DI)
unnamed: LED151.4 (DO), LED152.2 (DI)
unnamed: LED152.4 (DO), LED153.2 (DI)
unnamed: LED153.4 (DO), LED154.2 (DI)
unnamed: LED154.4 (DO), LED155.2 (DI)
unnamed: LED155.4 (DO), LED156.2 (DI)
unnamed: LED156.4 (DO), LED157.2 (DI)
unnamed: LED157.4 (DO), LED158.2 (DI)
unnamed: LED158.4 (DO), LED159.2 (DI)
unnamed: LED159.4 (DO), LED160.2 (DI)
unnamed: LED161.4 (DO), LED162.2 (DI)
unnamed: LED162.4 (DO), LED163.2 (DI)
unnamed: LED163.4 (DO), LED164.2 (DI)
unnamed: LED164.4 (DO), LED165.2 (DI)
unnamed: LED165.4 (DO), LED166.2 (DI)
unnamed: LED166.4 (DO), LED167.2 (DI)
unnamed: LED167.4 (DO), LED168.2 (DI)
unnamed: LED168.4 (DO), LED169.2 (DI)
unnamed: LED169.4 (DO), LED170.2 (DI)
unnamed: LED170.4 (DO), LED171.2 (DI)
unnamed: LED171.4 (DO), LED172.2 (DI)
unnamed: LED172.4 (DO), LED173.2 (DI)
unnamed: LED173.4 (DO), LED174.2 (DI)
unnamed: LED174.4 (DO), LED175.2 (DI)
unnamed: LED175.4 (DO), LED176.2 (DI)
unnamed: LED176.4 (DO), LED177.2 (DI)
unnamed: LED177.4 (DO), LED178.2 (DI)
unnamed: LED178.4 (DO), LED179.2 (DI)
unnamed: LED179.4 (DO), LED180.2 (DI)
unnamed: LED181.4 (DO), LED182.2 (DI)
unnamed: LED182.4 (DO), LED183.2 (DI)
unnamed: LED183.4 (DO), LED184.2 (DI)
unnamed: LED184.4 (DO), LED185.2 (DI)
unnamed: LED185.4 (DO), LED186.2 (DI)
unnamed: LED186.4 (DO), LED187.2 (DI)
unnamed: LED187.4 (DO), LED188.2 (DI)
unnamed: LED188.4 (DO), LED189.2 (DI)
unnamed: LED189.4 (DO), LED190.2 (DI)
unnamed: LED190.4 (DO), LED191.2 (DI)
unnamed: LED191.4 (DO), LED192.2 (DI)
unnamed: LED192.4 (DO), LED193.2 (DI)
unnamed: LED193.4 (DO), LED194.2 (DI)
unnamed: LED194.4 (DO), LED195.2 (DI)
unnamed: LED195.4 (DO), LED196.2 (DI)
unnamed: LED196.4 (DO), LED197.2 (DI)
unnamed: LED197.4 (DO), LED198.2 (DI)
unnamed: LED198.4 (DO), LED199.2 (DI)
unnamed: LED199.4 (DO), LED200.2 (DI)
unnamed: LED201.4 (DO), LED202.2 (DI)
unnamed: LED202.4 (DO), LED203.2 (DI)
unnamed: LED203.4 (DO), LED204.2 (DI)
unnamed: LED204.4 (DO), LED205.2 (DI)
unnamed: LED205.4 (DO), LED206.2 (DI)
unnamed: LED206.4 (DO), LED207.2 (DI)
unnamed: LED207.4 (DO), LED208.2 (DI)
unnamed: LED208.4 (DO), LED209.2 (DI)
unnamed: LED209.4 (DO), LED210.2 (DI)
unnamed: LED210.4 (DO), LED211.2 (DI)
unnamed: LED211.4 (DO), LED212.2 (DI)
unnamed: LED212.4 (DO), LED213.2 (DI)
unnamed: LED213.4 (DO), LED214.2 (DI)
unnamed: LED214.4 (DO), LED215.2 (DI)
unnamed: LED215.4 (DO), LED216.2 (DI)
unnamed: LED216.4 (DO), LED217.2 (DI)
unnamed: LED217.4 (DO), LED218.2 (DI)
unnamed: LED218.4 (DO), LED219.2 (DI)
unnamed: LED219.4 (DO), LED220.2 (DI)
unnamed: LED221.4 (DO), LED222.2 (DI)
unnamed: LED222.4 (DO), LED223.2 (DI)
unnamed: LED223.4 (DO), LED224.2 (DI)
unnamed: LED224.4 (DO), LED225.2 (DI)
unnamed: LED225.4 (DO), LED226.2 (DI)
unnamed: LED226.4 (DO), LED227.2 (DI)
unnamed: LED227.4 (DO), LED228.2 (DI)
unnamed: LED228.4 (DO), LED229.2 (DI)
unnamed: LED229.4 (DO), LED230.2 (DI)
unnamed: LED230.4 (DO), LED231.2 (DI)
unnamed: LED231.4 (DO), LED232.2 (DI)
unnamed: LED232.4 (DO), LED233.2 (DI)
unnamed: LED233.4 (DO), LED234.2 (DI)
unnamed: LED234.4 (DO), LED235.2 (DI)
unnamed: LED235.4 (DO), LED236.2 (DI)
unnamed: LED236.4 (DO), LED237.2 (DI)
unnamed: LED237.4 (DO), LED238.2 (DI)
unnamed: LED238.4 (DO), LED239.2 (DI)
unnamed: LED239.4 (DO), LED240.2 (DI)
unnamed: LED241.4 (DO), LED242.2 (DI)
unnamed: LED242.4 (DO), LED243.2 (DI)
unnamed: LED243.4 (DO), LED244.2 (DI)
unnamed: LED244.4 (DO), LED245.2 (DI)
unnamed: LED245.4 (DO), LED246.2 (DI)
unnamed: LED246.4 (DO), LED247.2 (DI)
unnamed: LED247.4 (DO), LED248.2 (DI)

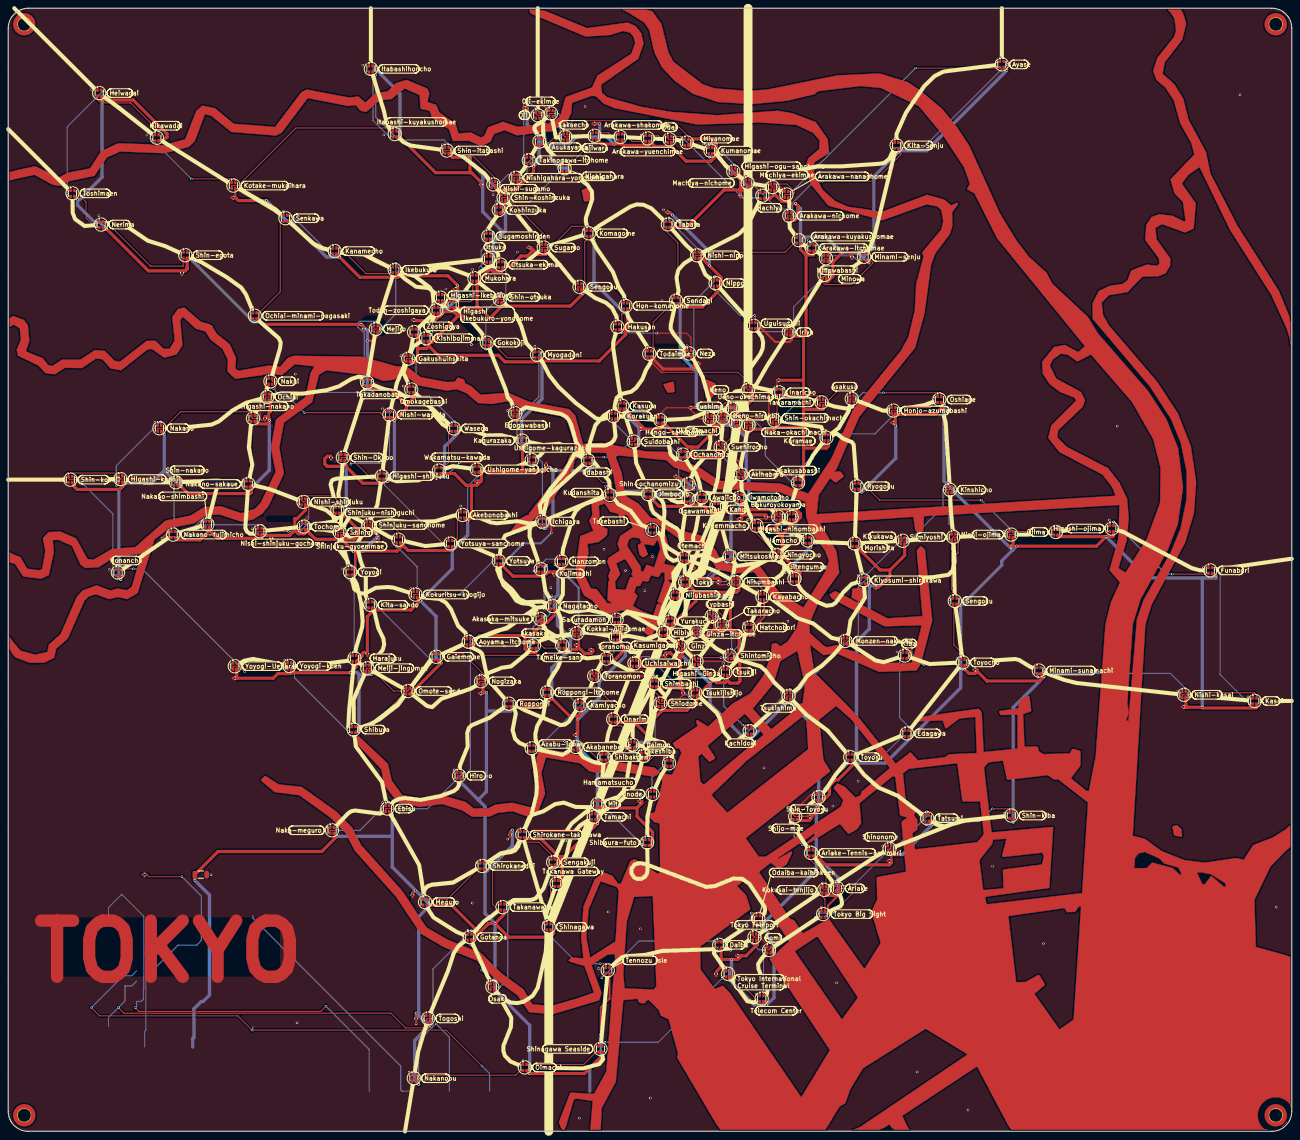
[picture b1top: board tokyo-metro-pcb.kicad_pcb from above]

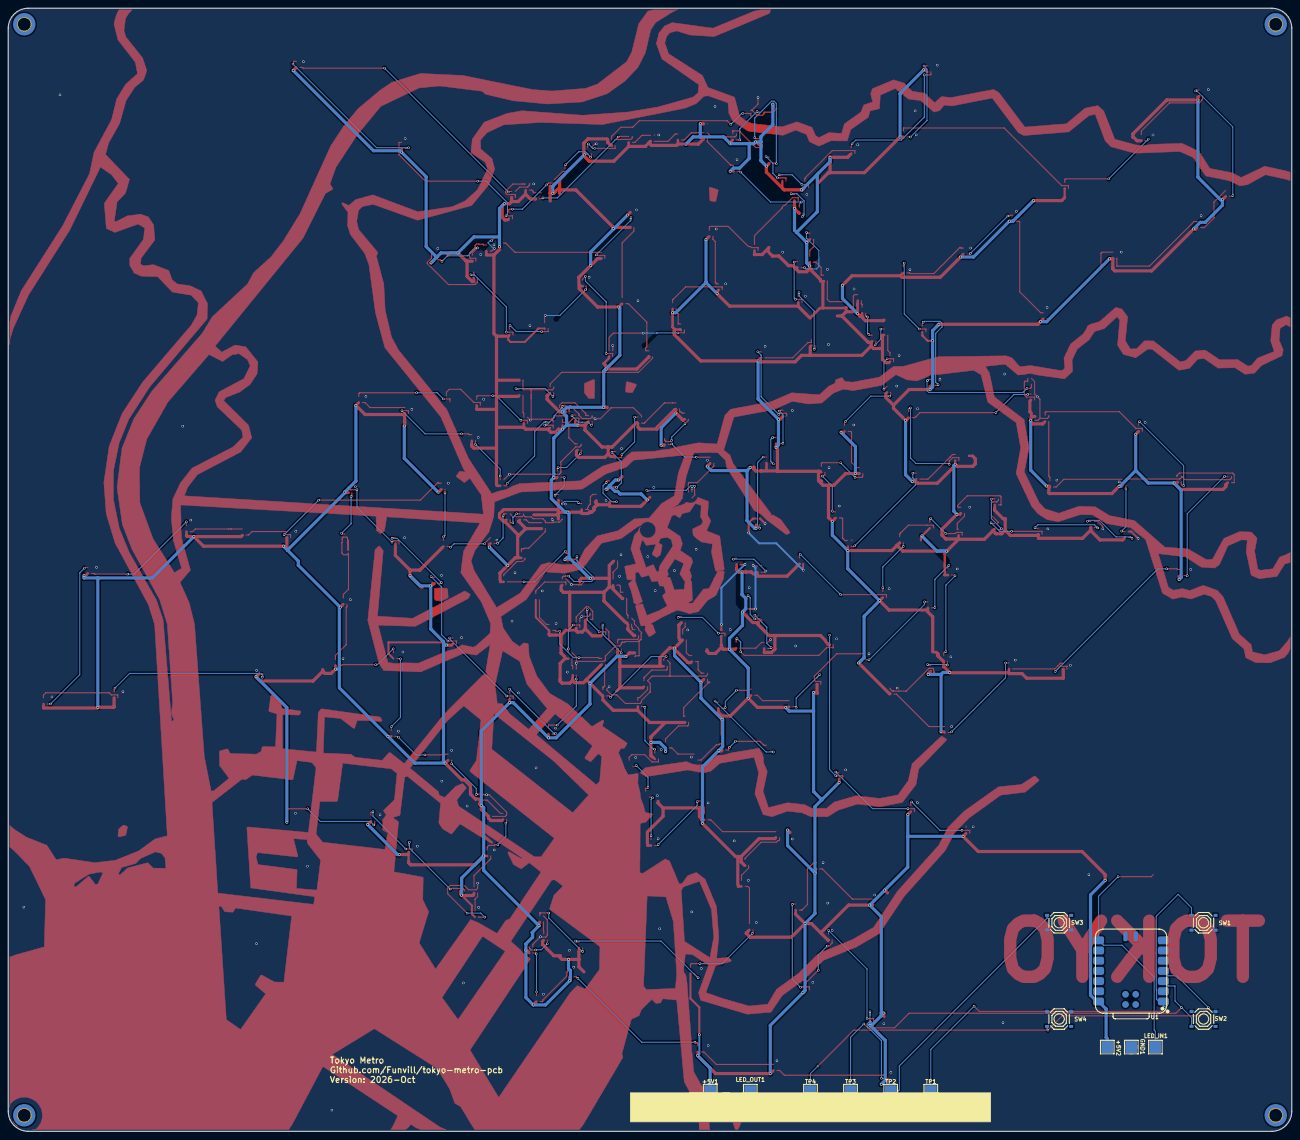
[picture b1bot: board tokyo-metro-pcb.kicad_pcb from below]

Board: 2 copper layers, 320.0 x 280.0 mm, 320 parts (14 on the bottom side), 256 nets.

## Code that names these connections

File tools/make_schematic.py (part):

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        # Montreal tied the chain's last output to the LED_OUT test point
        # with a second label, ROW8. With 13 rows this file generates a
        # ROW8 of its own, and the two shorted LED160 to the test point.
        # Generated boundary labels are CHAIN1..n, and any leftover ROW
        # label goes.
        if kind.startswith("global_label") and re.match(r'\(global_label "ROW\d+"', body):
            in_grid = True
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                          f"gl:out:{row}"))

    # --- tidy the inherited controller block ---------------------------
    # Montreal hangs LED_DATA and LED_IN straight off R1's two pins with no
    # wire, so both labels' text runs back across the resistor body, and
    # C1's value text runs through R1's reference. Electrically fine,
    # unreadable on paper. Give each label a stub to stand off on - a wire
    # from the pin to the label is the same net - and move C1's value text
    # clear. check_schematic.py counts what is left.
    # LED_DATA gets 2.54 mm, not 5.08: it stands above R1 and its text reads
    # upward, so at 5.08 the far end of the text reached BUTTON_01's label.
    # LED_IN reads downward into clear space and keeps the full 5.08.
    # Removing a block means finding that exact block, not matching a
    # pattern across the file: a lazy [\s\S]*? between the label's name and
    # its position happily spans from an earlier LED_DATA label all the way
    # to this one and deletes the entire controller block in between. It
    # did, and the netlist went from 281 components to 261 before
    # check_led_chain noticed R1 had gone.
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    body = body.rstrip()
    assert body.endswith(")"), "unexpected end of schematic"
    # `tidy` MUST go in with `gen`. Leaving it out deleted LED_DATA and
    # LED_IN from R1's pins and put nothing back, so the data path broke in
    # three places at once: GPIO1 dead-ended at its test point, both of
    # R1's pads fell to unconnected-(R1-Pad*), and LED1's DI sat on a
    # one-node net. The chain was still continuous end to end, which is all
    # check_led_chain.py asserts, so every check passed on a board where
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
